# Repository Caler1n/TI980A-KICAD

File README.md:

# TI980A KiCad

## Overview 

The goal of this project is to reproduce the TI980A schematics in KiCad. 

## Current Status

- Started additional I/O modules and backplane
- Arithmetic Unit Schematic Halfway Done

## Contributing
Contributions are welcome! If you have any corrections, additional modules, or PCB layouts, please open an issue or submit a pull request. 

## Resources
[Scanned Documentation](https://github.com/Caler1n/TI980A-Docs)

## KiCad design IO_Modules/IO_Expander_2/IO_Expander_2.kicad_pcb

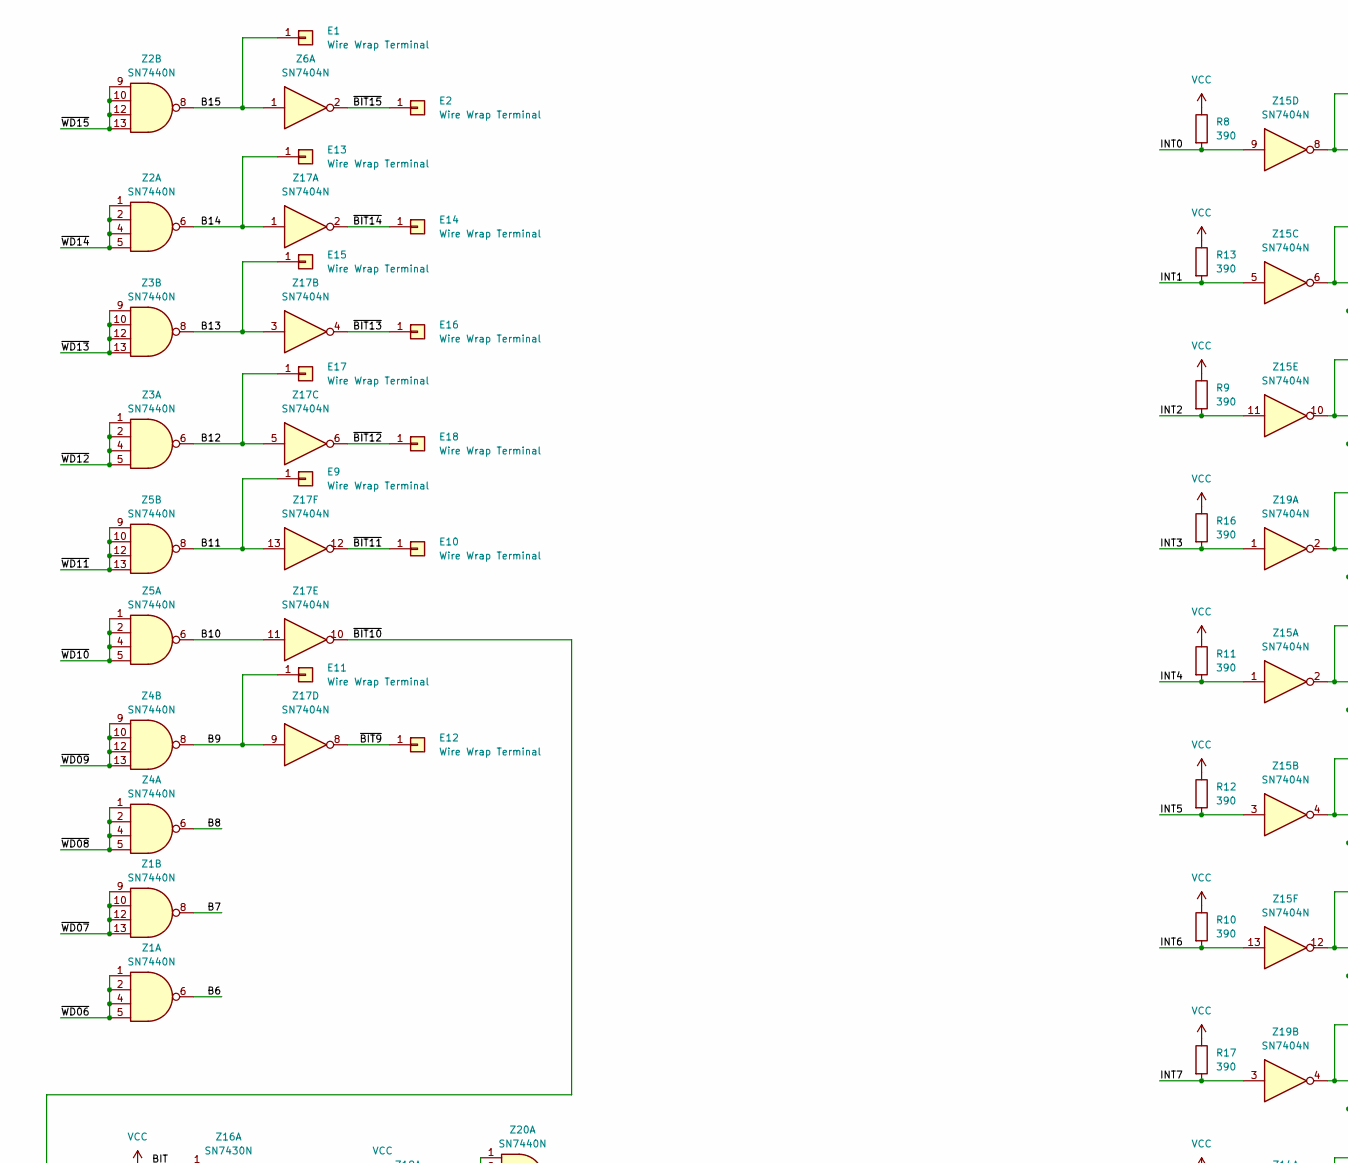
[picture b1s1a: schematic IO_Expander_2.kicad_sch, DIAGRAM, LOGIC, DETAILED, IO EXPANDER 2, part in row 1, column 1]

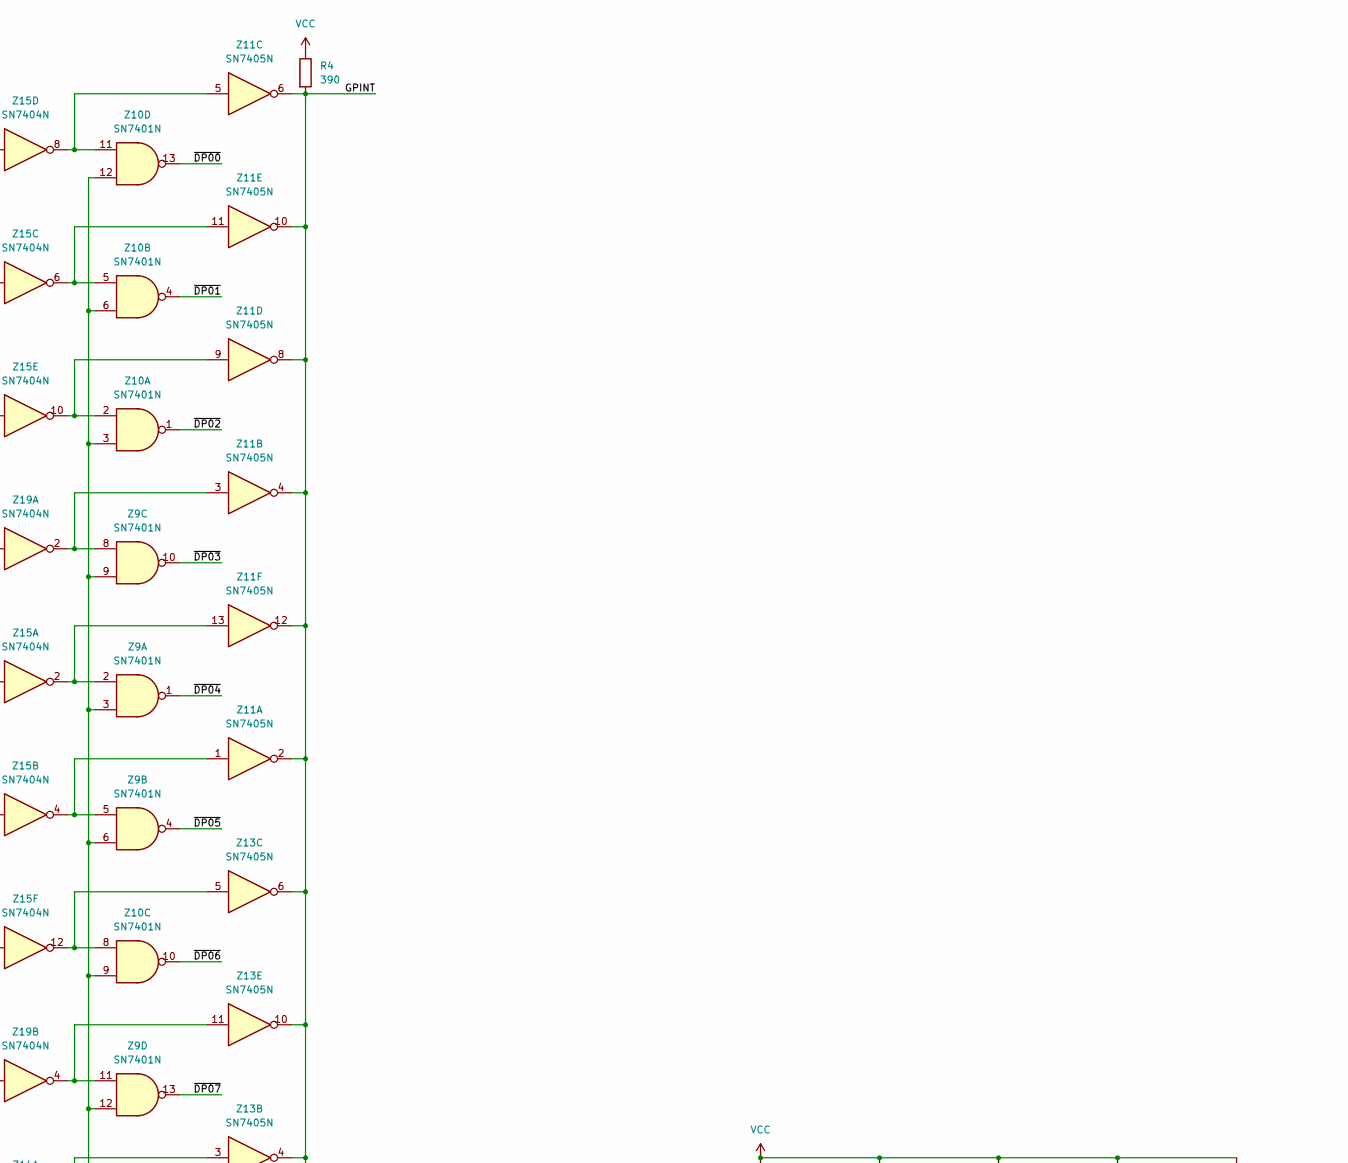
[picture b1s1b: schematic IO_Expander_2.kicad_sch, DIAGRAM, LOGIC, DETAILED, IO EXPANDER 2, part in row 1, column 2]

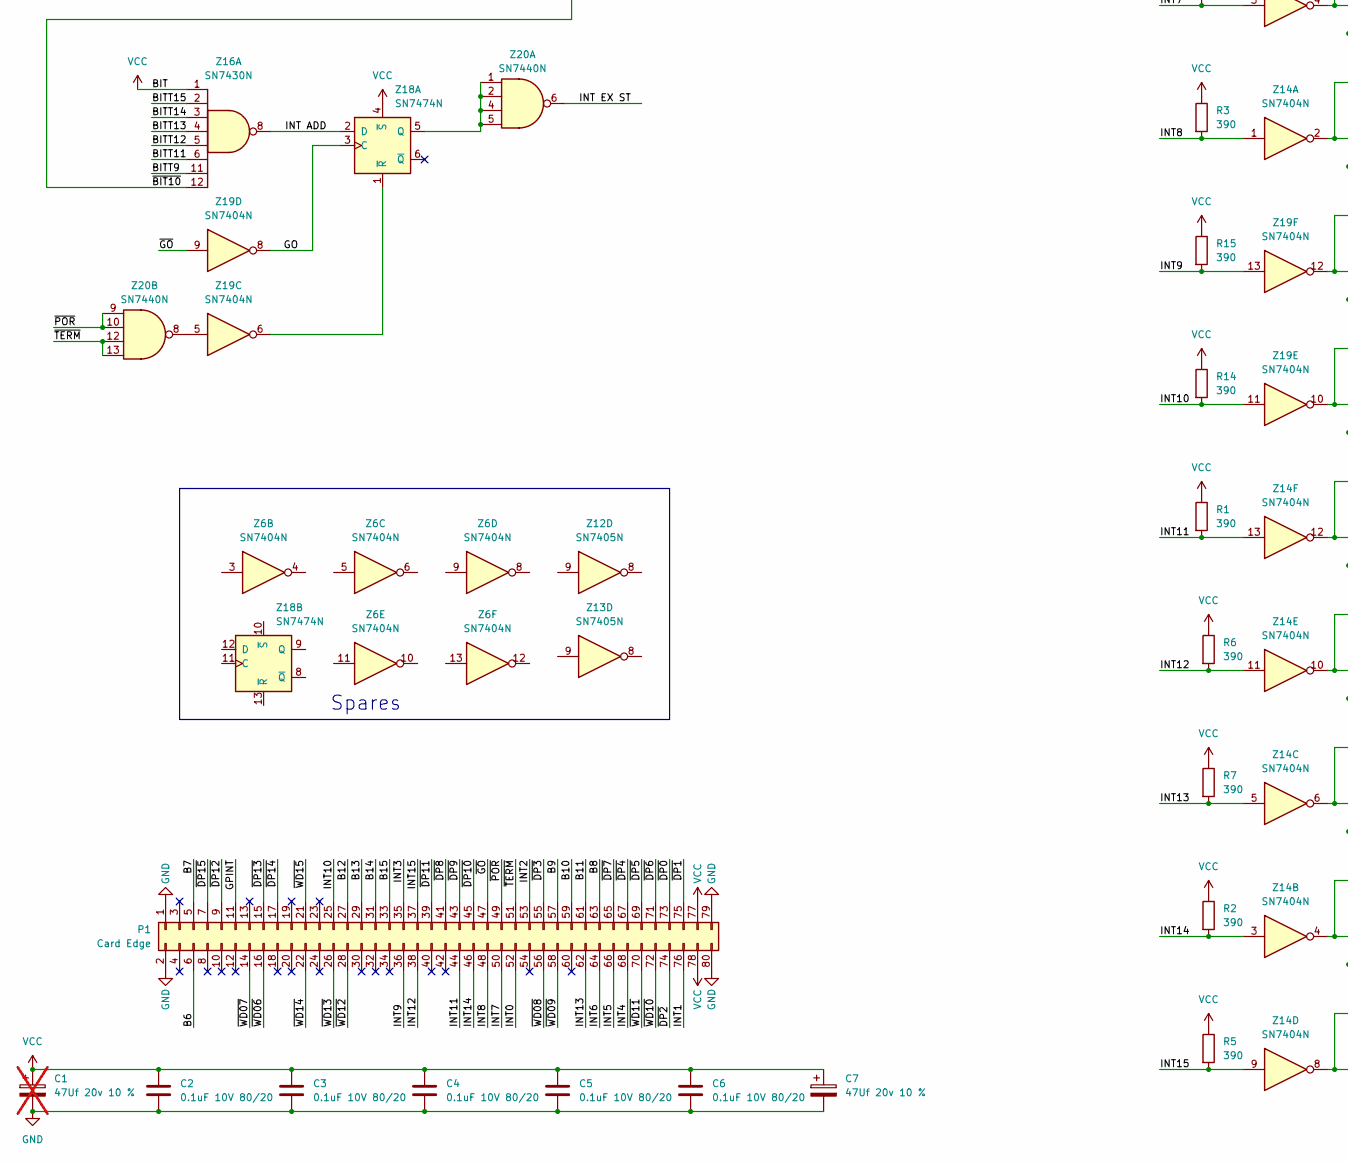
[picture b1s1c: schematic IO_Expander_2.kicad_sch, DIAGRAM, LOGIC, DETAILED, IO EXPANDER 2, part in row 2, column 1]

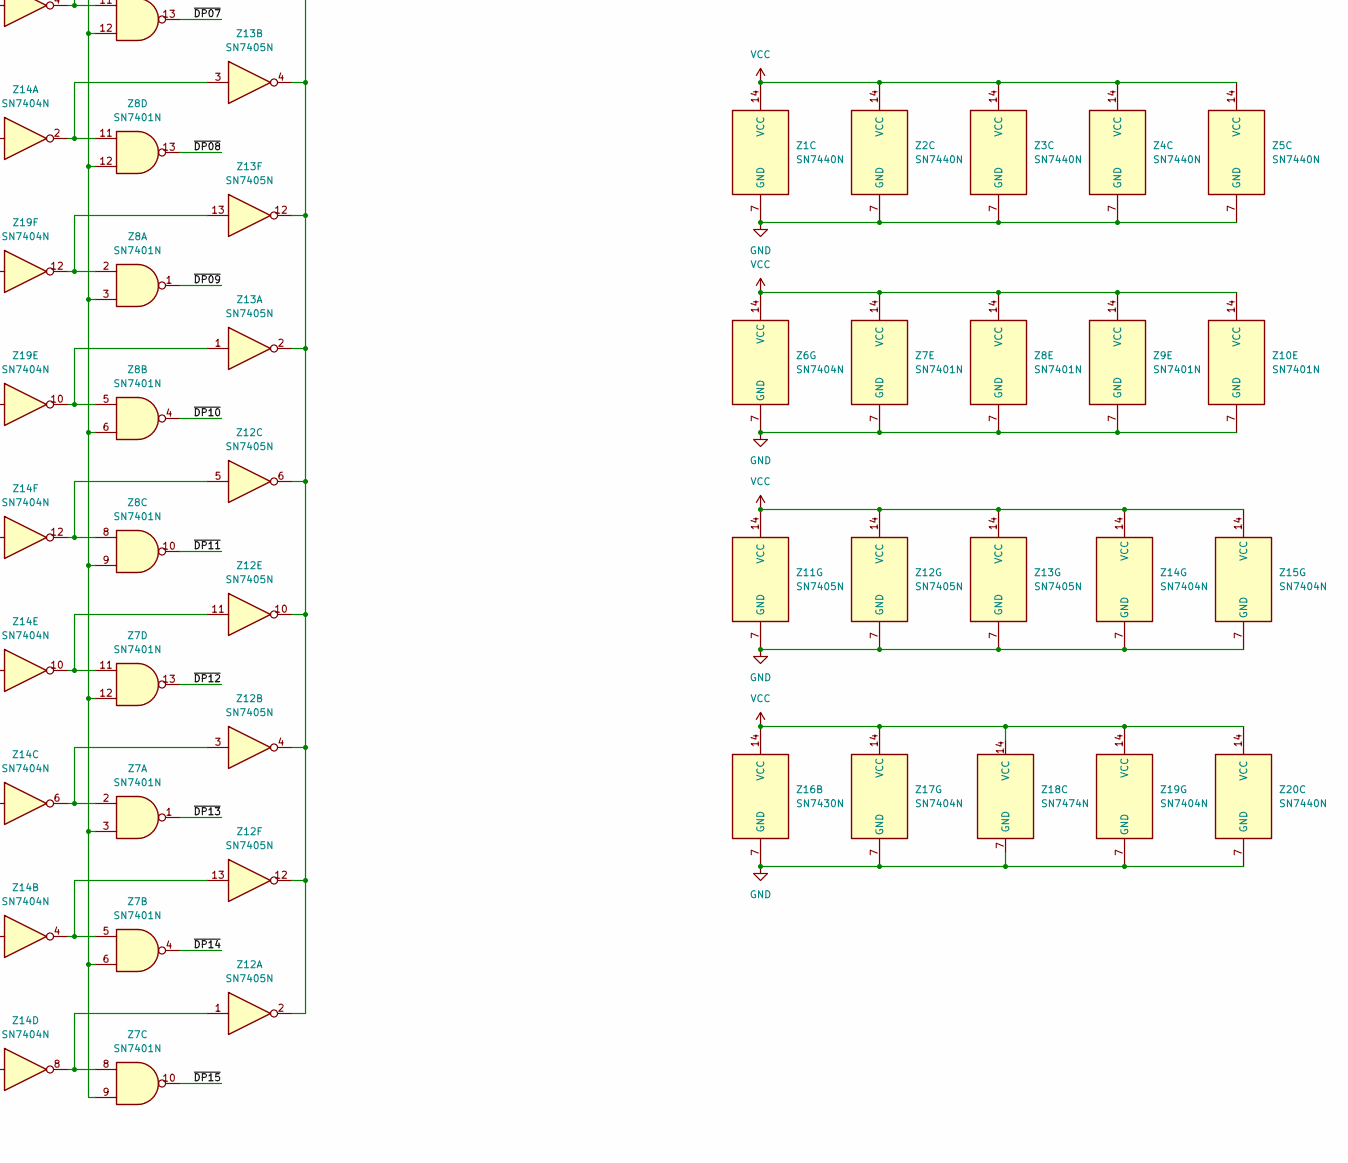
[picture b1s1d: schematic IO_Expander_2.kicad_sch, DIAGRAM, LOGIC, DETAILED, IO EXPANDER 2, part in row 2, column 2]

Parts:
C1: 47Uf 20v 10 %; CP_Axial_L11.0mm_D6.0mm_P18.00mm_Horizontal; not fitted
C2, C3, C4, C5, C6: 0.1uF 10V 80/20; C_Disc_D7.5mm_W2.5mm_P5.00mm
C7: 47Uf 20v 10 %; CP_Axial_L11.0mm_D6.0mm_P18.00mm_Horizontal
E1, E2, E9, E10, E11, E12, E13, E14, E15, E16, E17, E18: Wire Wrap Terminal; PinHeader_1x01_P2.54mm_Vertical
P1: Card Edge; Backplane-Connector
R1, R2, R3, R4, R5, R6, R7, R8, R9, R10, R11, R12, R13, R14, R15, R16, R17: 390; R_Axial_DIN0207_L6.3mm_D2.5mm_P10.16mm_Horizontal
Z1, Z2, Z3, Z4, Z5, Z20: SN7440N; DIP-14_W7.62mm_Socket_LongPads
Z6, Z14, Z15, Z17, Z19: SN7404N; DIP-14_W7.62mm_Socket_LongPads
Z7, Z8, Z9, Z10: SN7401N; DIP-14_W7.62mm_Socket_LongPads
Z11, Z12, Z13: SN7405N; DIP-14_W7.62mm_Socket_LongPads
Z16: SN7430N; DIP-14_W7.62mm_Socket_LongPads
Z18: SN7474N; DIP-14_W7.62mm_Socket_LongPads

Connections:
/<NO NET>: P1.72, Z5.1, Z5.2, Z5.4, Z5.5
/B6: P1.6, Z1.6
/B7: P1.5, Z1.8
/B8: P1.63, Z4.6
/B9: E11.1 (Pin_1_1), P1.57, Z4.8, Z17.9
/B10: P1.59, Z5.6, Z17.11
/B11: E9.1 (Pin_1_1), P1.61, Z5.8, Z17.13
/B12: E17.1 (Pin_1_1), P1.27, Z3.6, Z17.5
/B13: E15.1 (Pin_1_1), P1.29, Z3.8, Z17.3
/B14: E13.1 (Pin_1_1), P1.31, Z2.6, Z17.1
/B15: E1.1 (Pin_1_1), P1.33, Z2.8, Z6.1
/BITT9: Z16.11
/BITT11: Z16.6
/BITT12: Z16.5
/BITT13: Z16.4
/BITT14: Z16.3
/BITT15: Z16.2
/GO: Z18.3 (C), Z19.8
/GPINT: P1.11, R4.2, Z11.2, Z11.4, Z11.6, Z11.8, Z11.10, Z11.12, Z12.2, Z12.4, Z12.6, Z12.10, Z12.12, Z13.2, Z13.4, Z13.6, Z13.10, Z13.12
/INT0: P1.52, R8.2, Z15.9
/INT1: P1.76, R13.2, Z15.5
/INT2: P1.53, R9.2, Z15.11
/INT3: P1.35, R16.2, Z19.1
/INT4: P1.68, R11.2, Z15.1
/INT5: P1.66, R12.2, Z15.3
/INT6: P1.64, R10.2, Z15.13
/INT7: P1.50, R17.2, Z19.3
/INT8: P1.48, R3.2, Z14.1
/INT9: P1.36, R15.2, Z19.13
/INT10: P1.25, R14.2, Z19.11
/INT11: P1.44, R1.2, Z14.13
/INT12: P1.38, R6.2, Z14.11
/INT13: P1.62, R7.2, Z14.5
/INT14: P1.46, R2.2, Z14.3
/INT15: P1.37, R5.2, Z14.9
/INT ADD: Z16.8, Z18.2 (D)
/INT EX ST: Z20.6
/~BIT9: E12.1 (Pin_1_1), Z17.8
/~BIT10: Z16.12, Z17.10
/~BIT11: E10.1 (Pin_1_1), Z17.12
/~BIT12: E18.1 (Pin_1_1), Z17.6
/~BIT13: E16.1 (Pin_1_1), Z17.4
/~BIT14: E14.1 (Pin_1_1), Z17.2
/~BIT15: E2.1 (Pin_1_1), Z6.2
/~DP0: P1.73
/~DP00: Z10.13
/~DP1: P1.75
/~DP01: Z10.4
/~DP2: P1.74
/~DP02: Z10.1
/~DP03: Z9.10
/~DP3: P1.55
/~DP04: Z9.1
/~DP4: P1.67
/~DP05: Z9.4
/~DP5: P1.69
/~DP6: P1.71
/~DP06: Z10.10
/~DP07: Z9.13
/~DP7: P1.65
/~DP08: Z8.13
/~DP8: P1.41
/~DP09: Z8.1
/~DP9: P1.43
/~DP10: P1.45, Z8.4
/~DP11: P1.39, Z8.10
/~DP12: P1.9, Z7.13
/~DP13: P1.15, Z7.1
/~DP14: P1.17, Z7.4
/~DP15: P1.7, Z7.10
/~GO: P1.47, Z19.9
/~POR: P1.49, Z20.9, Z20.10
/~TERM: P1.51, Z20.12, Z20.13
/~WD06: P1.16, Z1.1, Z1.2, Z1.4, Z1.5
/~WD07: P1.14, Z1.9, Z1.10, Z1.12, Z1.13
/~WD08: P1.56, Z4.1, Z4.2, Z4.4, Z4.5
/~WD09: P1.58, Z4.9, Z4.10, Z4.12, Z4.13
/~WD11: P1.70, Z5.9, Z5.10, Z5.12, Z5.13
/~WD12: P1.28, Z3.1, Z3.2, Z3.4, Z3.5
/~WD13: P1.26, Z3.9, Z3.10, Z3.12, Z3.13
/~WD14: P1.22, Z2.1, Z2.2, Z2.4, Z2.5
/~WD15: P1.21, Z2.9, Z2.10, Z2.12, Z2.13
GND: C1.2, C2.1, C3.1, C4.1, C5.1, C6.1, C7.2, P1.1, P1.2, P1.79, P1.80, Z1.7 (GND), Z2.7 (GND), Z3.7 (GND), Z4.7 (GND), Z5.7 (GND), Z6.7 (GND), Z7.7 (GND), Z8.7 (GND), Z9.7 (GND), Z10.7 (GND), Z11.7 (GND), Z12.7 (GND), Z13.7 (GND), Z14.7 (GND), Z15.7 (GND), Z16.7 (GND), Z17.7 (GND), Z18.7 (GND), Z19.7 (GND), Z20.7 (GND)
unnamed: Z10.2, Z11.9, Z15.10
unnamed: Z10.5, Z11.11, Z15.6
unnamed: Z10.8, Z13.5, Z15.12
unnamed: Z10.11, Z11.5, Z15.8
unnamed: Z7.3, Z7.6, Z7.9, Z7.12, Z8.3, Z8.6, Z8.9, Z8.12, Z9.3, Z9.6, Z9.9, Z9.12, Z10.3, Z10.6, Z10.9, Z10.12
unnamed: Z9.5, Z11.1, Z15.4
unnamed: Z9.8, Z11.3, Z19.2
unnamed: Z9.2, Z11.13, Z15.2
unnamed: Z7.8, Z12.1, Z14.8
unnamed: Z7.2, Z12.3, Z14.6
unnamed: Z8.8, Z12.5, Z14.12
unnamed: Z7.11, Z12.11, Z14.10
unnamed: Z7.5, Z12.13, Z14.4
unnamed: Z8.5, Z13.1, Z19.10
unnamed: Z8.11, Z13.3, Z14.2
unnamed: Z9.11, Z13.11, Z19.4
unnamed: Z8.2, Z13.13, Z19.12
unnamed: Z18.5 (Q), Z20.1, Z20.2, Z20.4, Z20.5
unnamed: Z18.1 (~R), Z19.6
unnamed: Z19.5, Z20.8
VCC: C1.1, C2.2, C3.2, C4.2, C5.2, C6.2, C7.1, P1.77, P1.78, R1.1, R2.1, R3.1, R4.1, R5.1, R6.1, R7.1, R8.1, R9.1, R10.1, R11.1, R12.1, R13.1, R14.1, R15.1, R16.1, R17.1, Z1.14 (VCC), Z2.14 (VCC), Z3.14 (VCC), Z4.14 (VCC), Z5.14 (VCC), Z6.14 (VCC), Z7.14 (VCC), Z8.14 (VCC), Z9.14 (VCC), Z10.14 (VCC), Z11.14 (VCC), Z12.14 (VCC), Z13.14 (VCC), Z14.14 (VCC), Z15.14 (VCC), Z16.1, Z16.14 (VCC), Z17.14 (VCC), Z18.4 (~S), Z18.14 (VCC), Z19.14 (VCC), Z20.14 (VCC)

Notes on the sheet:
Spares

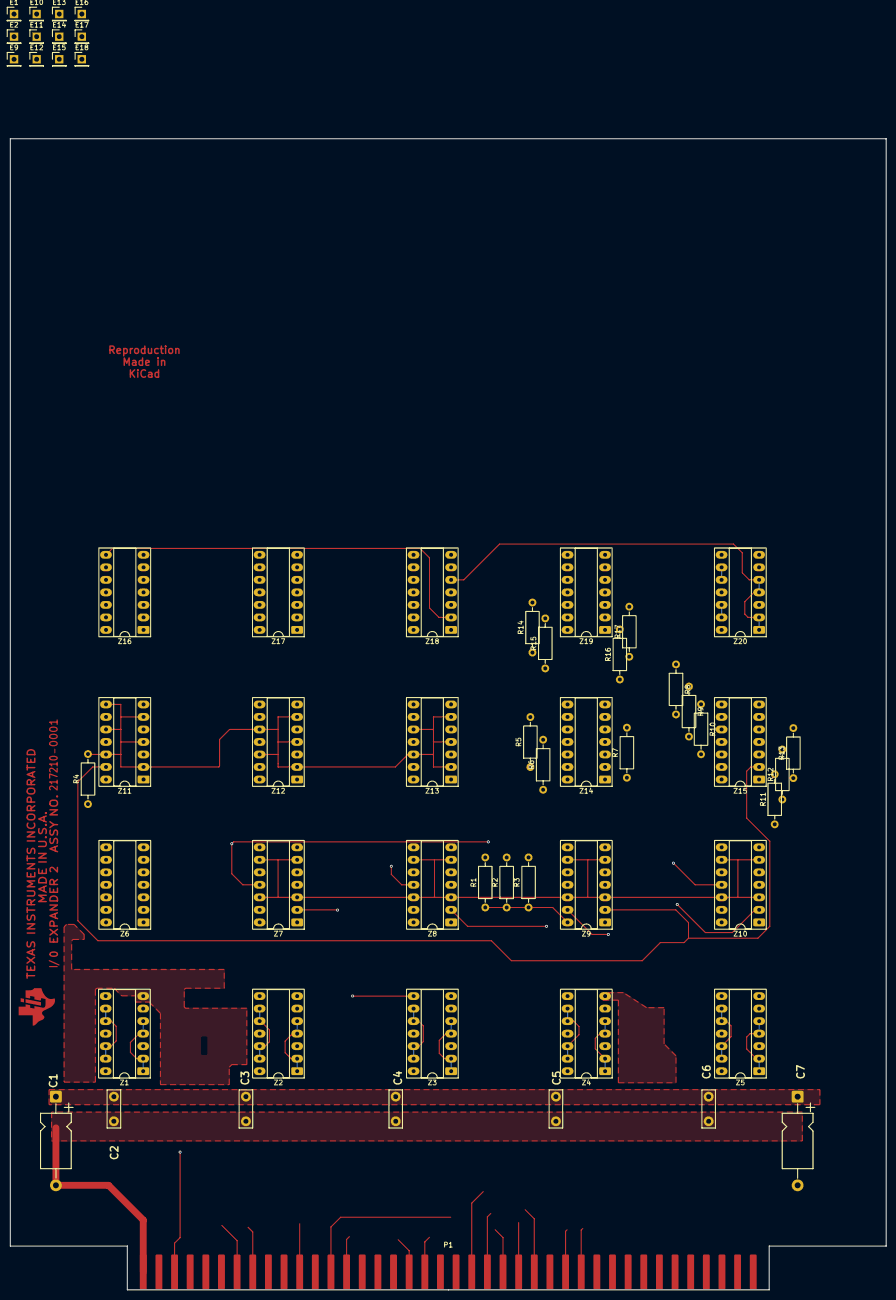
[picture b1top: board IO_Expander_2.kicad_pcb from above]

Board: 2 copper layers, 177.8 x 233.7 mm, 57 parts (0 on the bottom side), 77 nets.

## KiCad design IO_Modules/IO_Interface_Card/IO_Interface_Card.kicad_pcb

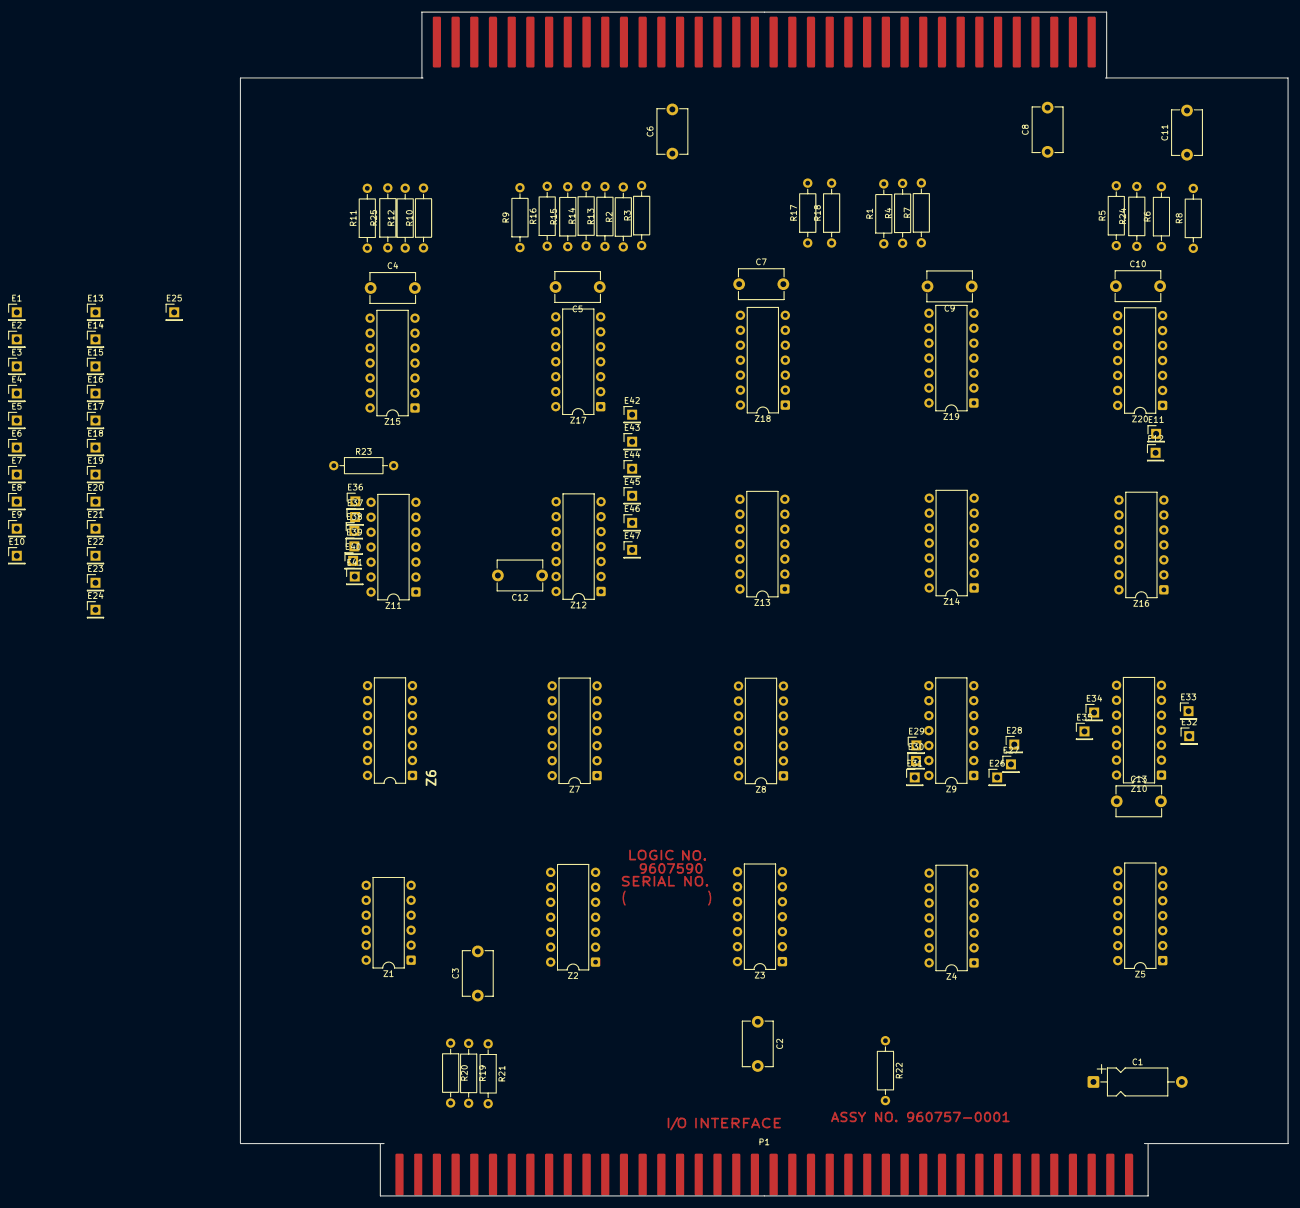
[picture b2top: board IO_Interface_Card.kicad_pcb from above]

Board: 2 copper layers, 177.8 x 200.9 mm, 107 parts (0 on the bottom side), 146 nets, no tracks yet.

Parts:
C1: 68uF 15V 10%; CP_Axial_L10.0mm_D4.5mm_P15.00mm_Horizontal
C2, C3, C4, C5, C6, C7, C8, C9, C10, C11, C12, C13: 50nF 12V 20%; C_Disc_D7.5mm_W5.0mm_P7.50mm
E1, E2, E3, E4, E5, E6, E7, E8, E9, E10, E11, E12, E13, E14, E15, E16, E17, E18, E19, E20, E21, E22, E23, E24, E25, E26, E27, E28, E29, E30, E31, E32, E33, E34, E35, E36, E37, E38, E39, E40, E41, E42, E43, E44, E45, E46, E47: Terminal; PinHeader_1x01_P2.54mm_Vertical
P1: Conn_02x40_Odd_Even; Backplane-Connector
P2: Conn_02x36_Top_Bottom; Type-2-Top-Edge-Connector
R1, R2, R3, R4, R5, R6, R7, R8, R9, R10, R11, R12, R13, R14, R15, R16, R17, R18: 82 1/4W 5%; R_Axial_DIN0207_L6.3mm_D2.5mm_P10.16mm_Horizontal
R19, R20, R21, R22: 1k 1/4W 5%; R_Axial_DIN0207_L6.3mm_D2.5mm_P10.16mm_Horizontal
R23, R25: 5.1k 1/4W 5%; R_Axial_DIN0207_L6.3mm_D2.5mm_P10.16mm_Horizontal
R24: 390 1/4W 5%; R_Axial_DIN0207_L6.3mm_D2.5mm_P10.16mm_Horizontal
Z1: SN7440N; DIP-12_W7.62mm
Z2, Z3: SN7400N; DIP-14_W7.62mm
Z4, Z11: SN7409N; DIP-14_W7.62mm
Z5, Z7, Z8: SN7401N; DIP-14_W7.62mm
Z6: SN74LS04N; DIP-14_W7.62mm
Z9: 74H103N; DIP-14_W7.62mm
Z10, Z12, Z14: SN7404N; DIP-14_W7.62mm
Z13: SN7430N; DIP-14_W7.62mm
Z15: SN7402N; DIP-14_W7.62mm
Z16, Z17, Z18, Z19, Z20: SN74H04N; DIP-14_W7.62mm

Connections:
/E: P2.10, Z5.3
/ENINTINT: Z2.2, Z2.13, Z3.2, Z3.13, Z9.9 (Q)
/F: P2.12, Z2.4
/GOIO: Z13.6, Z14.9, Z14.10
/H: P2.14, R6.2
/INT1: Z2.1, Z6.2
/INT2: Z2.12, Z6.4
/INT3: Z3.1, Z6.6
/INT4: Z3.12, Z6.12
/INTINT: Z1.6, Z6.11
/IOUT0: P1.25, Z12.9
/IOUT1: P1.23, Z12.5
/IOUT2: P1.20, Z12.3
/IOUT3: P1.19, Z12.1
/IOUT4: P1.11, Z12.13
/IOUT5: P1.13, Z16.13
/IOUT5A: E18.1 (Pin_1_1), E27.1 (Pin_1_1), Z9.2 (~R), Z15.9, Z16.9, Z16.10
/IOUT6: P1.6, Z16.1
/IOUT6A: E16.1 (Pin_1_1), E26.1 (Pin_1_1), Z9.1 (CLK), Z15.8, Z16.4, Z16.5
/IOUT7: P1.5, Z12.11
/IOUT8: P1.63, Z10.5
/IOUT9: P1.57, Z18.1
/IOUT9A: E14.1 (Pin_1_1), E20.1 (Pin_1_1), Z13.3, Z18.4, Z18.5
/IOUT10: P1.59, Z20.1
/IOUT10A: Z15.2, Z20.4, Z20.5
/IOUT11: P1.61, Z20.13
/IOUT11A: E10.1 (Pin_1_1), E22.1 (Pin_1_1), Z13.5, Z20.9, Z20.10
/IOUT12: P1.27, Z19.13
/IOUT12A: E8.1 (Pin_1_1), E19.1 (Pin_1_1), Z13.2, Z19.9, Z19.10
/IOUT13: P1.29, Z17.13
/IOUT13A: E6.1 (Pin_1_1), E24.1 (Pin_1_1), Z13.12, Z17.9, Z17.10
/IOUT14: P1.31, Z17.1
/IOUT14A: E4.1 (Pin_1_1), E23.1 (Pin_1_1), Z13.11, Z17.4, Z17.5
/IOUT15: P1.33, Z19.1
/IOUT15A: E2.1 (Pin_1_1), E21.1 (Pin_1_1), Z13.4, Z19.4, Z19.5
/J: P2.16, R5.2
/K: P2.18, R7.2
/L: P2.20, R8.2
/M: P2.22, Z5.6
/N: P2.24, Z5.8
/P: P2.26, Z3.9
/P2-15: C11.1, P2.29, R24.2, Z10.1, Z10.13
/R: P2.28, Z3.4
/RESET: Z14.4, Z14.5, Z15.11
/RRDINT: Z9.10 (K), Z10.8
/S: P2.30, R18.2
/SYSCLKA: Z6.8, Z9.5 (CLK)
/T: P2.32, R17.2
/TERMIO: Z14.2, Z14.13, Z15.12
/V: P2.36, Z14.12
/X: R25.2, Z11.4
/Y: R23.2, Z11.2
/~DP0: P1.73, Z5.1
/~DP1: P1.75, Z4.3
/~DP2A: P2.27, Z2.9
/~DP2: P1.74, Z4.6
/~DP3: P1.55, Z4.11
/~DP4: P1.67, Z4.8
/~DP5A: P2.23, Z5.11
/~DP5: P1.69, Z5.13
/~DP6: P1.71, Z5.4
/~DP7: P1.65, Z5.10
/~DP8: P1.41, Z7.10
/~DP9: P1.43, Z7.4
/~DP10: P1.45, Z7.1
/~DP11: P1.39, Z7.13
/~DP12: P1.9, Z8.13
/~DP13: P1.15, Z8.4
/~DP14: P1.17, Z8.1
/~DP15: P1.7, Z8.10
/~GOIO: P1.47, Z14.11
/~INT1: P1.8, P1.53, R19.2, R22.2, Z1.1, Z1.5, Z6.1, Z6.13
/~INT2: P1.10, R20.2, Z1.2, Z6.3
/~INT3: P1.12, R21.2, Z1.4, Z6.5
/~INTINT: Z6.10, Z11.1
/~IOINT: P1.35, Z11.3
/~IOUT5A: E17.1 (Pin_1_1), Z16.11, Z16.12
/~IOUT6A: E15.1 (Pin_1_1), Z16.2, Z16.3
/~IOUT9A: E13.1 (Pin_1_1), Z18.2, Z18.3
/~IOUT10A: Z20.2, Z20.3
/~IOUT11A: E9.1 (Pin_1_1), Z20.11, Z20.12
/~IOUT12A: E7.1 (Pin_1_1), Z19.11, Z19.12
/~IOUT13A: E5.1 (Pin_1_1), Z17.11, Z17.12
/~IOUT14A: E3.1 (Pin_1_1), Z17.2, Z17.3
/~IOUT15A: E1.1 (Pin_1_1), Z19.2, Z19.3
/~READYIO: P1.37, Z11.6
/~RESET: P1.49, Z14.3
/~RRINT: Z10.9, Z15.13
/~SYSCLK: P1.21, Z1.9, Z6.9
/~TERMIO: P1.51, Z14.1
GND: C1.2, C2.2, C3.2, C4.2, C5.2, C6.2, C7.2, C8.2, C9.2, C10.2, C11.2, C12.2, C13.2, P1.1, P1.2, P1.79, P1.80, P2.3, P2.5, P2.7, P2.9, P2.11, P2.13, P2.15, P2.17, P2.19, P2.21, P2.25, P2.31, P2.33, P2.35, Z1.7 (GND_7), Z2.7 (GND), Z3.7 (GND), Z4.7 (GND), Z5.7 (GND), Z6.7 (GND), Z7.7 (GND), Z8.7 (GND), Z9.11 (GND), Z10.7 (GND), Z11.7 (GND), Z12.7 (GND), Z13.7 (GND), Z14.7 (GND), Z15.7 (GND), Z16.7 (GND), Z17.7 (GND), Z18.7 (GND), Z19.7 (GND), Z20.7 (GND)
unnamed: E11.1 (Pin_1_1), Z15.5
unnamed: E12.1 (Pin_1_1), Z15.6
unnamed: E25.1 (Pin_1_1), Z15.4
unnamed: E28.1 (Pin_1_1), Z9.3 (K)
unnamed: E29.1 (Pin_1_1), Z9.12 (Q)
unnamed: E30.1 (Pin_1_1), Z9.13 (~Q)
unnamed: E31.1 (Pin_1_1), Z9.14 (J)
unnamed: E32.1 (Pin_1_1), Z10.3
unnamed: E33.1 (Pin_1_1), Z10.4
unnamed: E34.1 (Pin_1_1), Z10.10
unnamed: E35.1 (Pin_1_1), Z10.11
unnamed: E36.1 (Pin_1_1), Z11.8
unnamed: E37.1 (Pin_1_1), Z11.9
unnamed: E38.1 (Pin_1_1), Z11.10
unnamed: E39.1 (Pin_1_1), Z11.11
unnamed: E40.1 (Pin_1_1), Z11.12
unnamed: E41.1 (Pin_1_1), Z11.13
unnamed: E42.1 (Pin_1_1), Z18.8
unnamed: E43.1 (Pin_1_1), Z18.9
unnamed: E44.1 (Pin_1_1), Z18.10
unnamed: E45.1 (Pin_1_1), Z18.11
unnamed: E46.1 (Pin_1_1), Z18.12
unnamed: E47.1 (Pin_1_1), Z18.13
unnamed: R1.1, Z19.6
unnamed: R2.1, Z17.6
unnamed: R3.1, Z17.8
unnamed: R4.1, Z19.8
unnamed: R5.1, Z20.8
unnamed: R6.1, Z20.6
unnamed: R7.1, Z18.6
unnamed: R8.1, Z10.6
unnamed: R9.2, Z12.10
unnamed: R10.1, Z16.6
unnamed: R11.1, Z16.8
unnamed: R12.1, Z12.12
unnamed: R13.1, Z12.2
unnamed: R14.1, Z12.4
unnamed: R15.1, Z12.6
unnamed: R16.1, Z12.8
unnamed: R17.1, Z14.8
unnamed: R18.1, Z14.6
unnamed: Z2.3, Z4.1
unnamed: Z2.6, Z4.2
unnamed: Z2.8, Z4.4
unnamed: Z2.11, Z4.5
unnamed: Z3.3, Z4.13
unnamed: Z3.6, Z4.12
unnamed: Z3.8, Z4.10
unnamed: Z3.11, Z4.9
unnamed: Z9.7 (J), Z15.1
unnamed: Z2.5, Z2.10, Z3.5, Z3.10, Z5.2, Z5.5, Z5.9, Z5.12, Z10.2
unnamed: Z7.3, Z7.6, Z7.9, Z7.12, Z8.3, Z8.6, Z8.9, Z8.12, Z10.12
unnamed: Z13.1, Z15.10
unnamed: Z13.8, Z15.3
VCC: C1.1, C2.1, C3.1, C4.1, C5.1, C6.1, C7.1, C8.1, C9.1, C10.1, C12.1, C13.1, P1.77, P1.78, R19.1, R20.1, R21.1, R22.1, R23.1, R24.1, R25.1, Z1.10, Z1.12, Z2.14 (VCC), Z3.14 (VCC), Z4.14 (VCC), Z5.14 (VCC), Z6.14 (VCC), Z7.14 (VCC), Z8.14 (VCC), Z9.4 (VCC), Z9.6 (~R), Z10.14 (VCC), Z11.5, Z11.14 (VCC), Z12.14 (VCC), Z13.14 (VCC), Z14.14 (VCC), Z15.14 (VCC), Z16.14 (VCC), Z17.14 (VCC), Z18.14 (VCC), Z19.14 (VCC), Z20.14 (VCC)
